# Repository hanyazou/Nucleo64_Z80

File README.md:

# Nucleo64 Z80

Nucleo64 Z80 is a Z80 expansion board for the STM32 Nucleo 64 board.
It adds a Z80 CPU and SRAM to the Nucleo.
The Z80's I/O access is handled by the STM32 MCU on the Nucleo.

## Features

- Simple 2-chip configuration with Z80 and SRAM, no additional logic IC needed
- Board test firmware includes Microsoft BASIC
- Faster Z80 CPU execution (clock up to 20MHz)
- I2C and SPI devices can be used with the Z80 (custom firmware required)

The Nucleo64 Z80 is derived from satoshiokue's MEZ80RAM and SuperMEZ80-CPM.

## Appearance

The white boards in the following pictures are the Nucleo64 Z80.

## Block Diagram

## Required Components

### ICs

- U3 Z80 (DIP 40 pin) *1
- U2 AS6C4008-55 SRAM 4Mbit (DIP 32 pin) *2

### Through-hole Components

- U3 IC socket (DIP 40 pin)
- U2 IC socket (DIP 32 pin)
- C1, C2 Capacitors 0.1uF
- R1 Resistor 200 ohms
- J4, J5 Pin headers (0.1" pitch 19x2 pin)
- D3, D4, D5 LEDs
- R6, R7, R8 Resistors 100 ohms 1/4W (resistor value may vary depending on the LED)

### Optional Components

- J3 SH 1.0 JST 4 pin connector *3
- J4, J5 Pin sockets (0.1" pitch 6x1 pin) *4

*1) Z80C0004 (4MHz) or higher recommended  
*2) 512Kbit (64KB) might be sufficient  
*3) For I2C Qwiic devices  
*4) For the micro SD card slot, use the one for ARM Arduino as shown on the following page:  
https://www.amazon.com/dp/B0B7WZQVHS

## Build Instructions

With fewer components, assembly is straightforward.
Solder all components except the 19x2 pin headers first, then solder the pin headers last.

## Board Test Firmware

The `FW/board_test` folder contains a test firmware project for STM32 CubeIDE.
The current target is STM32 Nucleo-64 STM32L476RG.

This firmware includes Microsoft BASIC.
When the Z80 runs at 20 MHz, executing ASCIIARTM.BAS takes 61 seconds.

The Z80 clock is generated by TIM5 in the STM32 L476RG.
The prescaler of TIM5 is set to 10 - 1, so the Z80 runs at 4 MHz, which is 1/20 of the system clock (80 MHz).
If you change the prescaler to 1, the clock will be 20 MHz.

## References

### SuperMEZ80-CPM

https://github.com/hanyazou/SuperMEZ80-CPM

### EMUZ80

https://vintagechips.wordpress.com/2022/03/05/emuz80_reference/

### MEZ80RAM

https://github.com/satoshiokue/MEZ80RAM

### NUCLEO-L476RG

https://www.st.com/en/evaluation-tools/nucleo-l476rg.html

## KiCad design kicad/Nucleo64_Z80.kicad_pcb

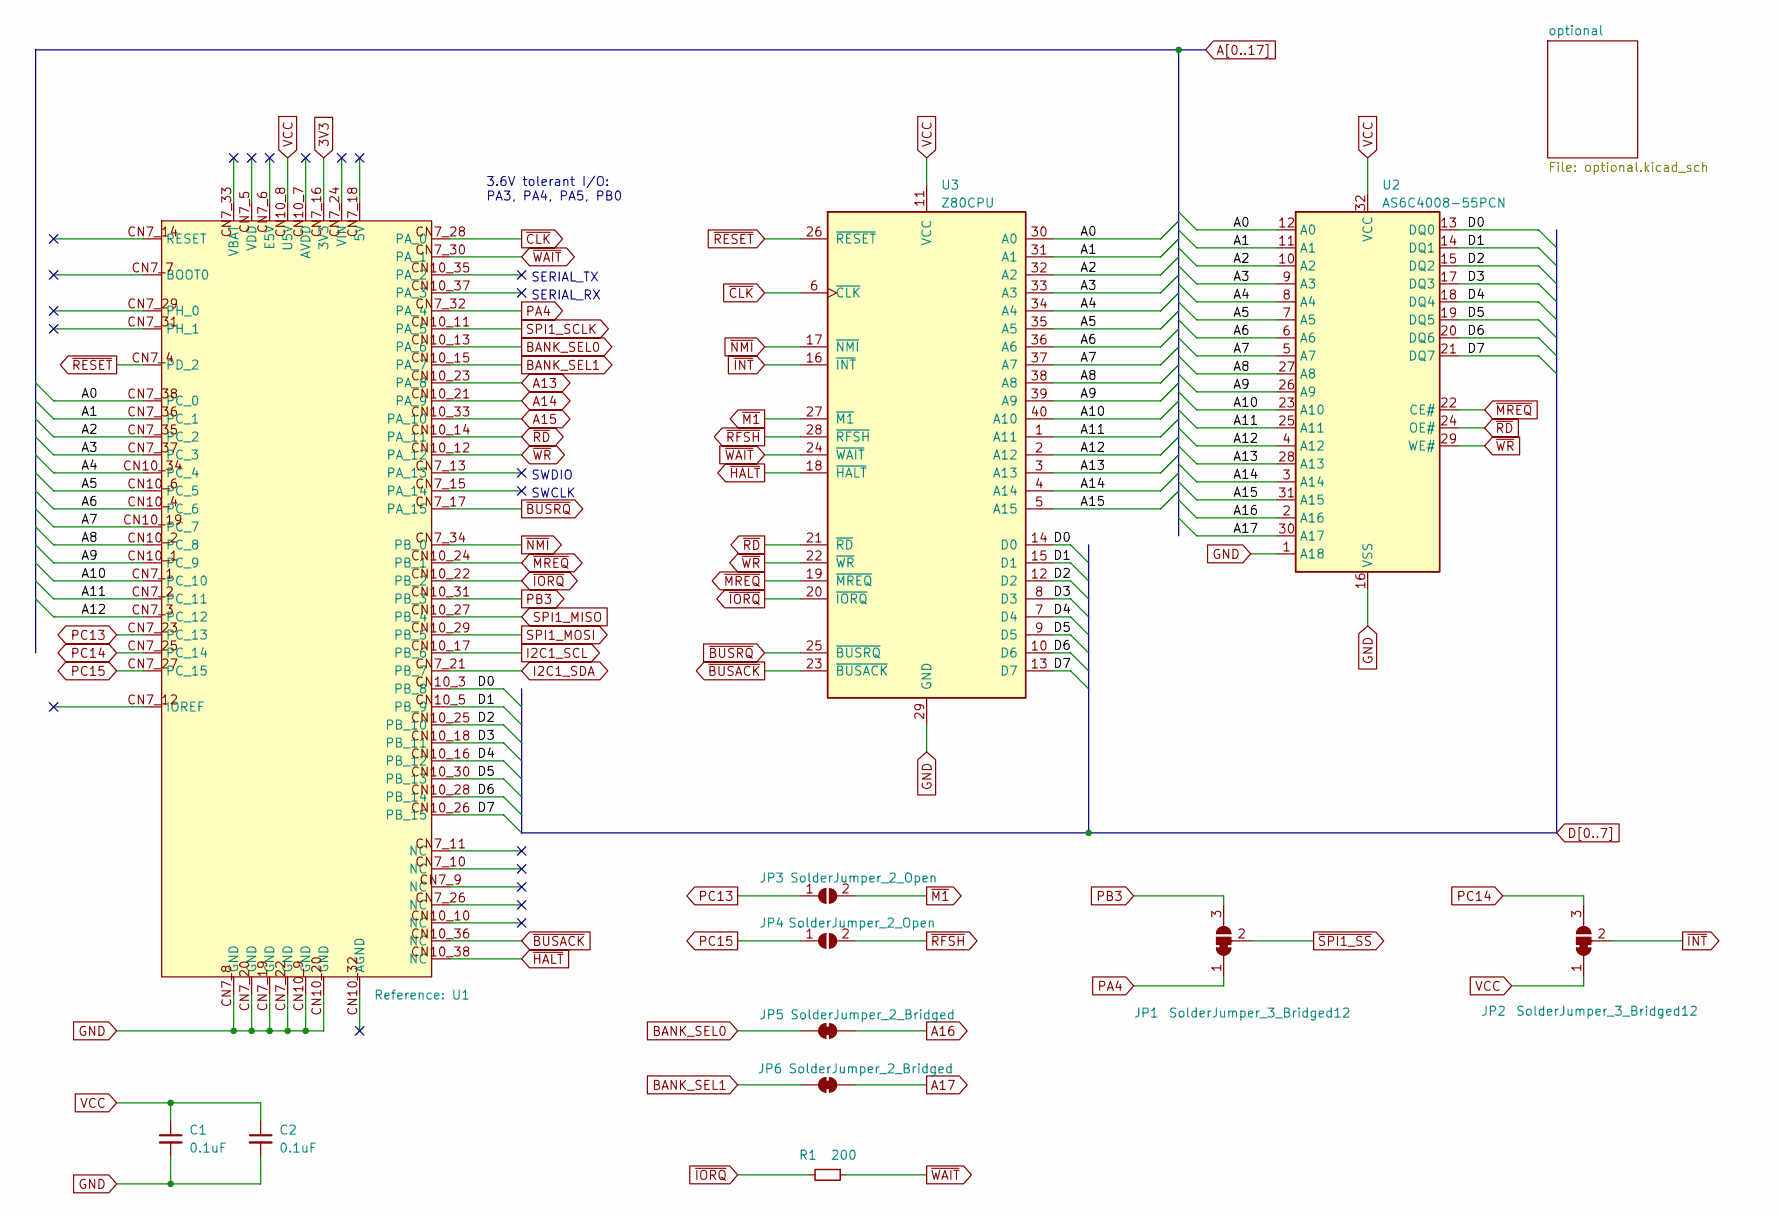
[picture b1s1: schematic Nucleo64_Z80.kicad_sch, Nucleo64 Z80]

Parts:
C1, C2: 0.1uF; C_Disc_D3.8mm_W2.6mm_P2.50mm
JP1, JP2: SolderJumper_3_Bridged12; SolderJumper-3_P1.3mm_Bridged12_RoundedPad1.0x1.5mm_NumberL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
JP3, JP4: SolderJumper_2_Open; SolderJumper-2_P1.3mm_Open_RoundedPad1.0x1.5mm
JP5, JP6: SolderJumper_2_Bridged; SolderJumper-2_P1.3mm_Bridged_RoundedPad1.0x1.5mm
R1: 200; R_Axial_DIN0204_L3.6mm_D1.6mm_P7.62mm_Horizontal
U1: NUCLEO64_morpho
U2: AS6C4008-55PCN; DIP-32_W15.24mm
U3: Z80CPU; DIP-40_W15.24mm

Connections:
3V3: U1.CN7_16 (3V3); also elsewhere on the board
A0: U1.CN7_38 (PC_0), U2.12 (A0), U3.30 (A0); also elsewhere on the board
A1: U1.CN7_36 (PC_1), U2.11 (A1), U3.31 (A1); also elsewhere on the board
A2: U1.CN7_35 (PC_2), U2.10 (A2), U3.32 (A2); also elsewhere on the board
A3: U1.CN7_37 (PC_3), U2.9 (A3), U3.33 (A3); also elsewhere on the board
A4: U1.CN10_34 (PC_4), U2.8 (A4), U3.34 (A4); also elsewhere on the board
A5: U1.CN10_6 (PC_5), U2.7 (A5), U3.35 (A5); also elsewhere on the board
A6: U1.CN10_4 (PC_6), U2.6 (A6), U3.36 (A6); also elsewhere on the board
A7: U1.CN10_19 (PC_7), U2.5 (A7), U3.37 (A7); also elsewhere on the board
A8: U1.CN10_2 (PC_8), U2.27 (A8), U3.38 (A8); also elsewhere on the board
A9: U1.CN10_1 (PC_9), U2.26 (A9), U3.39 (A9); also elsewhere on the board
A10: U1.CN7_1 (PC_10), U2.23 (A10), U3.40 (A10); also elsewhere on the board
A11: U1.CN7_2 (PC_11), U2.25 (A11), U3.1 (A11); also elsewhere on the board
A12: U1.CN7_3 (PC_12), U2.4 (A12), U3.2 (A12); also elsewhere on the board
A13: U1.CN10_23 (PA_8), U2.28 (A13), U3.3 (A13); also elsewhere on the board
A14: U1.CN10_21 (PA_9), U2.3 (A14), U3.4 (A14); also elsewhere on the board
A15: U1.CN10_33 (PA_10), U2.31 (A15), U3.5 (A15); also elsewhere on the board
A16: JP5.2 (B), U2.2 (A16); also elsewhere on the board
A17: JP6.2 (B), U2.30 (A17); also elsewhere on the board
BANK_SEL0: JP5.1 (A), U1.CN10_13 (PA_6); also elsewhere on the board
BANK_SEL1: JP6.1 (A), U1.CN10_15 (PA_7); also elsewhere on the board
D0: U1.CN10_3 (PB_8), U2.13 (DQ0), U3.14 (D0); also elsewhere on the board
D1: U1.CN10_5 (PB_9), U2.14 (DQ1), U3.15 (D1); also elsewhere on the board
D2: U1.CN10_25 (PB_10), U2.15 (DQ2), U3.12 (D2); also elsewhere on the board
D3: U1.CN10_18 (PB_11), U2.17 (DQ3), U3.8 (D3); also elsewhere on the board
D4: U1.CN10_16 (PB_12), U2.18 (DQ4), U3.7 (D4); also elsewhere on the board
D5: U1.CN10_30 (PB_13), U2.19 (DQ5), U3.9 (D5); also elsewhere on the board
D6: U1.CN10_28 (PB_14), U2.20 (DQ6), U3.10 (D6); also elsewhere on the board
D7: U1.CN10_26 (PB_15), U2.21 (DQ7), U3.13 (D7); also elsewhere on the board
GND: C1.2, C2.2, U1.CN7_8 (GND), U1.CN7_19 (GND), U1.CN7_20 (GND), U1.CN7_22 (GND), U1.CN10_9 (GND), U1.CN10_20 (GND), U2.1 (A18), U2.16 (VSS), U3.29 (GND); also elsewhere on the board
I2C1_SCL: U1.CN10_17 (PB_6); also elsewhere on the board
I2C1_SDA: U1.CN7_21 (PB_7); also elsewhere on the board
PA4: JP1.1 (A), U1.CN7_32 (PA_4)
PB3: JP1.3 (B), U1.CN10_31 (PB_3)
PC13: JP3.1 (A), U1.CN7_23 (PC_13)
PC14: JP2.3 (B), U1.CN7_25 (PC_14)
PC15: JP4.1 (A), U1.CN7_27 (PC_15)
SPI1_MISO: U1.CN10_27 (PB_4); also elsewhere on the board
SPI1_MOSI: U1.CN10_29 (PB_5); also elsewhere on the board
SPI1_SCLK: U1.CN10_11 (PA_5); also elsewhere on the board
VCC: C1.1, C2.1, JP2.1 (A), U1.CN10_8 (U5V), U2.32 (VCC), U3.11 (VCC); also elsewhere on the board
~BUSACK: U1.CN10_36 (NC), U3.23 (~BUSACK); also elsewhere on the board
~BUSRQ: U1.CN7_17 (PA_15), U3.25 (~BUSRQ); also elsewhere on the board
~CLK: U1.CN7_28 (PA_0), U3.6 (~CLK); also elsewhere on the board
~HALT: U1.CN10_38 (NC), U3.18 (~HALT); also elsewhere on the board
~INT: JP2.2 (C), U3.16 (~INT); also elsewhere on the board
~IORQ: R1.2, U1.CN10_22 (PB_2), U3.20 (~IORQ); also elsewhere on the board
~M1: JP3.2 (B), U3.27 (~M1); also elsewhere on the board
~MREQ: U1.CN10_24 (PB_1), U2.22 (CE#), U3.19 (~MREQ); also elsewhere on the board
~NMI: U1.CN7_34 (PB_0), U3.17 (~NMI); also elsewhere on the board
~RD: U1.CN10_14 (PA_11), U2.24 (OE#), U3.21 (~RD); also elsewhere on the board
~RESET: U1.CN7_4 (PD_2), U3.26 (~RESET); also elsewhere on the board
~RFSH: JP4.2 (B), U3.28 (~RFSH); also elsewhere on the board
~SPI1_SS: JP1.2 (C); also elsewhere on the board
~WAIT: R1.1, U1.CN7_30 (PA_1), U3.24 (~WAIT); also elsewhere on the board
~WR: U1.CN10_12 (PA_12), U2.29 (WE#), U3.22 (~WR); also elsewhere on the board

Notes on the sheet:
SWDIO
SERIAL_RX
SERIAL_TX
SWCLK
3.6V tolerant I/O: PA3, PA4, PA5, PB0

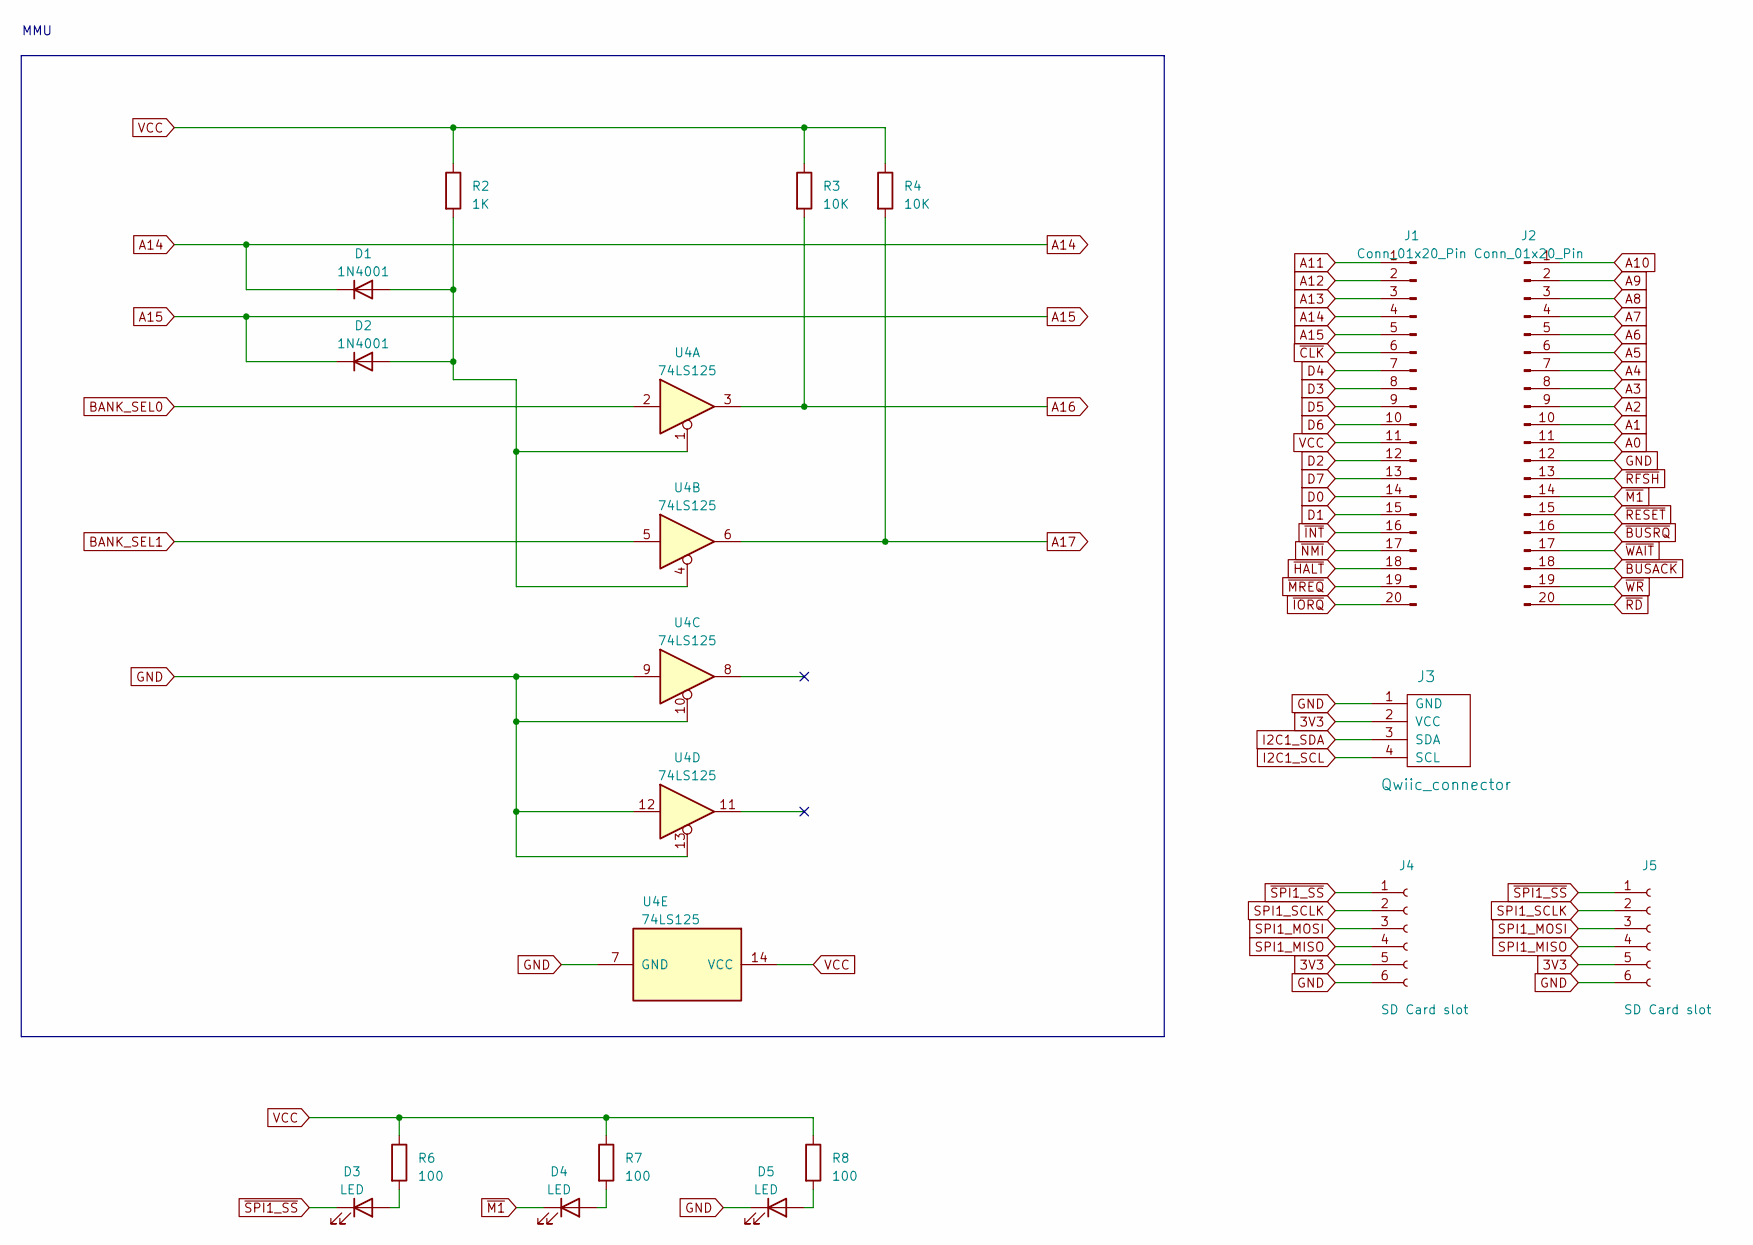
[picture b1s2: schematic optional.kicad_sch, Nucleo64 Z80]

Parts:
D1, D2: 1N4001; D_0805_2012Metric_Pad1.15x1.40mm_HandSolder
D3, D4, D5: LED; LED_D5.0mm
J1, J2: Conn_01x20_Pin; PinHeader_1x20_P2.54mm_Vertical
J3: Qwiic_connector; Qwiic_I2C_1.00mm_4pin
J4, J5: SD Card slot; PinHeader_1x06_P2.54mm_Vertical
R2: 1K; R_0805_2012Metric_Pad1.20x1.40mm_HandSolder
R3, R4: 10K; R_0805_2012Metric_Pad1.20x1.40mm_HandSolder
R6, R7, R8: 100; R_Axial_DIN0204_L3.6mm_D1.6mm_P7.62mm_Horizontal
U4: 74LS125; SSOP-14_5.3x6.2mm_P0.65mm

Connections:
3V3: J3.2 (VCC), J4.5, J5.5; also elsewhere on the board
A0: J2.11; also elsewhere on the board
A1: J2.10; also elsewhere on the board
A2: J2.9; also elsewhere on the board
A3: J2.8; also elsewhere on the board
A4: J2.7; also elsewhere on the board
A5: J2.6; also elsewhere on the board
A6: J2.5; also elsewhere on the board
A7: J2.4; also elsewhere on the board
A8: J2.3; also elsewhere on the board
A9: J2.2; also elsewhere on the board
A10: J2.1; also elsewhere on the board
A11: J1.1; also elsewhere on the board
A12: J1.2; also elsewhere on the board
A13: J1.3; also elsewhere on the board
A14: D1.1 (K), J1.4; also elsewhere on the board
A15: D2.1 (K), J1.5; also elsewhere on the board
A16: R3.2, U4.3; also elsewhere on the board
A17: R4.2, U4.6; also elsewhere on the board
BANK_SEL0: U4.2; also elsewhere on the board
BANK_SEL1: U4.5; also elsewhere on the board
D0: J1.14; also elsewhere on the board
D1: J1.15; also elsewhere on the board
D2: J1.12; also elsewhere on the board
D3: J1.8; also elsewhere on the board
D4: J1.7; also elsewhere on the board
D5: J1.9; also elsewhere on the board
D6: J1.10; also elsewhere on the board
D7: J1.13; also elsewhere on the board
GND: D5.1 (K), J2.12, J3.1 (GND), J4.6, J5.6, U4.7 (GND), U4.9, U4.10, U4.12, U4.13; also elsewhere on the board
I2C1_SCL: J3.4 (SCL); also elsewhere on the board
I2C1_SDA: J3.3 (SDA); also elsewhere on the board
unnamed: D1.2 (A), D2.2 (A), R2.2, U4.1, U4.4
unnamed: D3.2 (A), R6.2
unnamed: D4.2 (A), R7.2
unnamed: D5.2 (A), R8.2
SPI1_MISO: J4.4, J5.4; also elsewhere on the board
SPI1_MOSI: J4.3, J5.3; also elsewhere on the board
SPI1_SCLK: J4.2, J5.2; also elsewhere on the board
VCC: J1.11, R2.1, R3.1, R4.1, R6.1, R7.1, R8.1, U4.14 (VCC); also elsewhere on the board
~BUSACK: J2.18; also elsewhere on the board
~BUSRQ: J2.16; also elsewhere on the board
~CLK: J1.6; also elsewhere on the board
~HALT: J1.18; also elsewhere on the board
~INT: J1.16; also elsewhere on the board
~IORQ: J1.20; also elsewhere on the board
~M1: D4.1 (K), J2.14; also elsewhere on the board
~MREQ: J1.19; also elsewhere on the board
~NMI: J1.17; also elsewhere on the board
~RD: J2.20; also elsewhere on the board
~RESET: J2.15; also elsewhere on the board
~RFSH: J2.13; also elsewhere on the board
~SPI1_SS: D3.1 (K), J4.1, J5.1; also elsewhere on the board
~WAIT: J2.17; also elsewhere on the board
~WR: J2.19; also elsewhere on the board

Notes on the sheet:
MMU

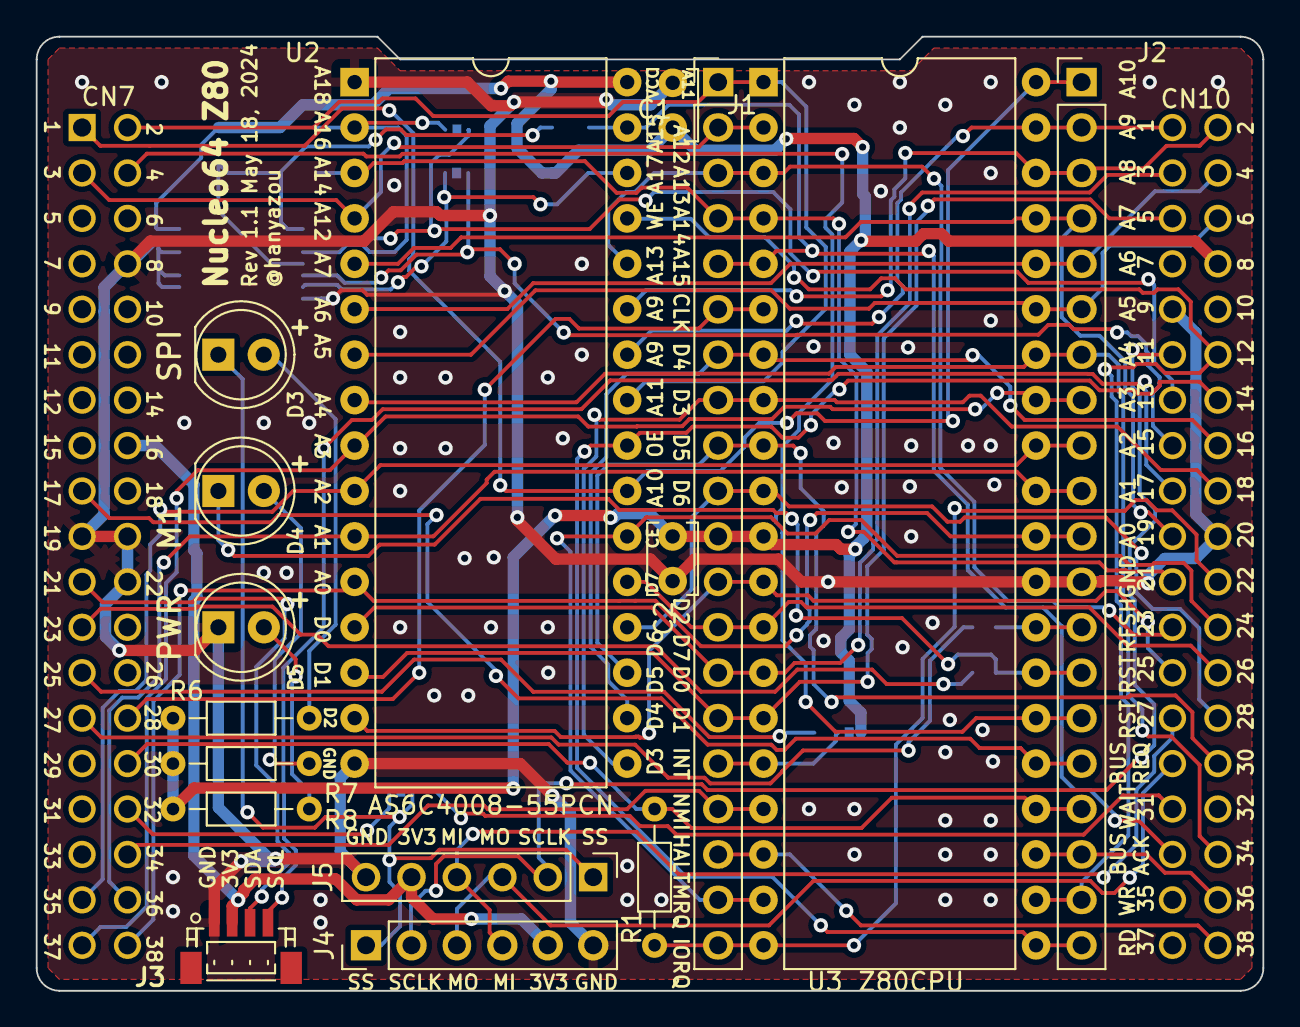
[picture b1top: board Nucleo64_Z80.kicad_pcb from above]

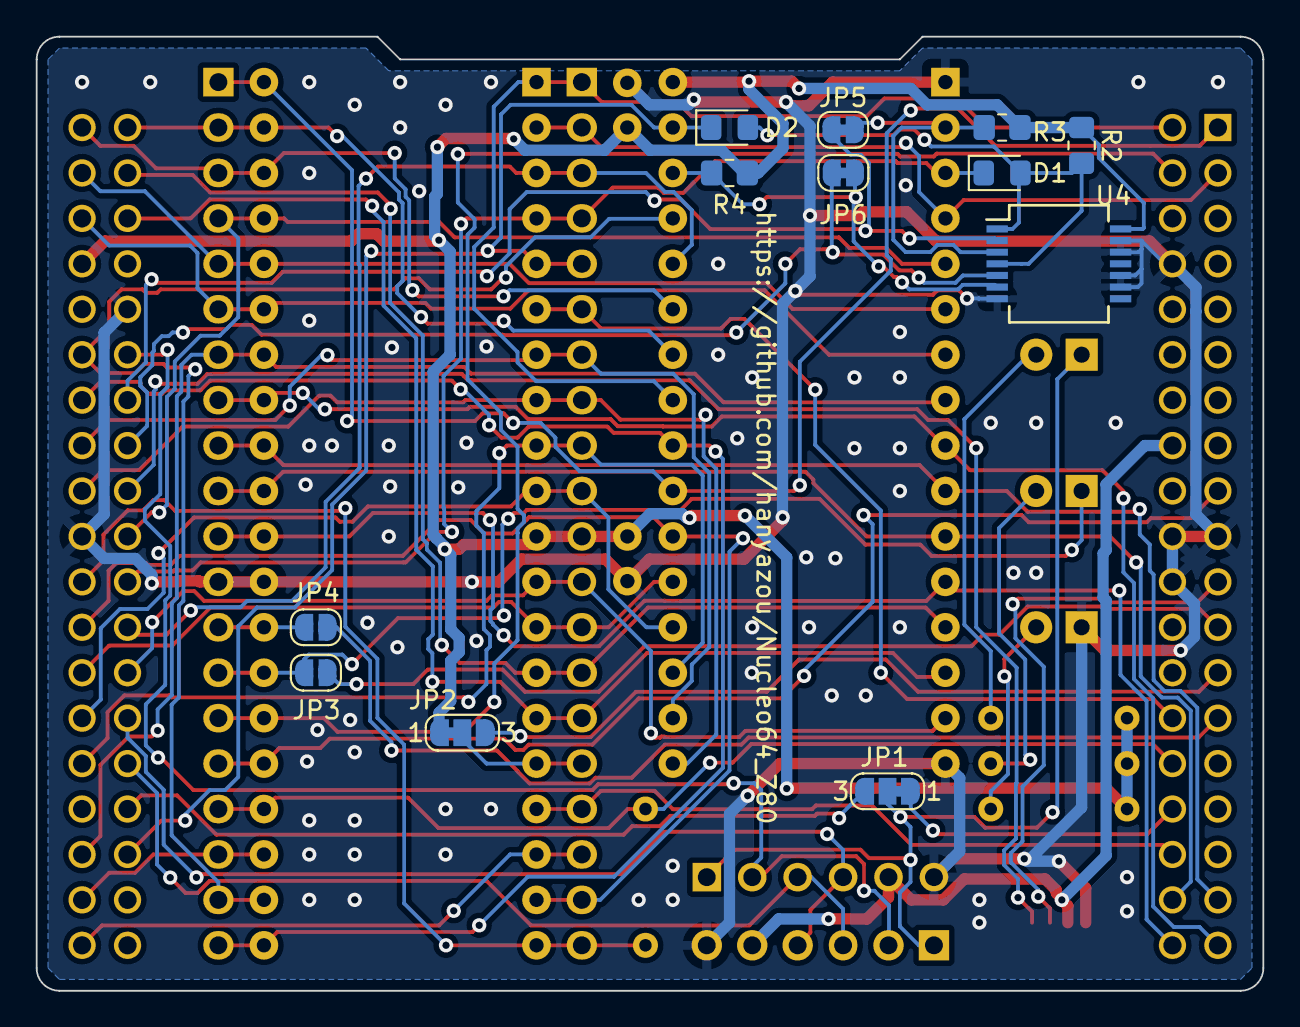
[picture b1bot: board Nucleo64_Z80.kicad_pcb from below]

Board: 2 copper layers, 68.6 x 53.3 mm, 29 parts (12 on the bottom side), 60 nets.

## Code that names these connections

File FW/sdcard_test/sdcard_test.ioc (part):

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Mcu.Name=STM32L476R(C-E-G)Tx
Mcu.Package=LQFP64
Mcu.UserName=STM32L476RGTx
PA0.Signal=S_TIM5_CH1
PA1.GPIOParameters=GPIO_PuPd,GPIO_Label
PA1.GPIO_Label=Z80_WAIT
PA1.GPIO_PuPd=GPIO_PULLUP
PA1.Signal=GPIO_Input
PA10.GPIOParameters=GPIO_PuPd,GPIO_Label
PA10.GPIO_Label=Z80_A15
PA10.GPIO_PuPd=GPIO_NOPULL
PA10.Signal=GPIO_Input
PA11.GPIOParameters=GPIO_PuPd,GPIO_Label
PA11.GPIO_Label=Z80_RD
PA11.GPIO_PuPd=GPIO_PULLUP
PA11.Signal=GPIO_Input
PA12.GPIOParameters=GPIO_PuPd,GPIO_Label
PA12.GPIO_Label=Z80_WR
PA12.GPIO_PuPd=GPIO_PULLUP
PA12.Signal=GPIO_Input
PA13\ (JTMS-SWDIO).GPIOParameters=GPIO_Label
PA13\ (JTMS-SWDIO).GPIO_Label=TMS
PA13\ (JTMS-SWDIO).Mode=Serial_Wire
PA13\ (JTMS-SWDIO).Signal=SYS_JTMS-SWDIO
PA14\ (JTCK-SWCLK).GPIOParameters=GPIO_Label
PA14\ (JTCK-SWCLK).GPIO_Label=TCK
PA14\ (JTCK-SWCLK).Mode=Serial_Wire
PA14\ (JTCK-SWCLK).Signal=SYS_JTCK-SWCLK
PA15\ (JTDI).GPIOParameters=GPIO_Label
PA15\ (JTDI).GPIO_Label=Z80_BUSRQ
PA15\ (JTDI).Signal=GPIO_Output
PA2.GPIOParameters=GPIO_Speed,GPIO_PuPd,GPIO_Label,GPIO_Mode
PA2.GPIO_Label=USART_TX
PA2.GPIO_Mode=GPIO_MODE_AF_PP
PA2.GPIO_PuPd=GPIO_NOPULL
PA2.GPIO_Speed=GPIO_SPEED_FREQ_VERY_HIGH
PA2.Mode=Asynchronous
PA2.Signal=USART2_TX
PA3.GPIOParameters=GPIO_Speed,GPIO_PuPd,GPIO_Label,GPIO_Mode
PA3.GPIO_Label=USART_RX
PA3.GPIO_Mode=GPIO_MODE_AF_PP
PA3.GPIO_PuPd=GPIO_NOPULL
PA3.GPIO_Speed=GPIO_SPEED_FREQ_VERY_HIGH
PA3.Mode=Asynchronous
PA3.Signal=USART2_RX
PA4.GPIOParameters=PinState,GPIO_Label
PA4.GPIO_Label=SPI1_SS
PA4.PinState=GPIO_PIN_SET
PA4.Signal=GPIO_Output
PA5.Mode=Full_Duplex_Master
PA5.Signal=SPI1_SCK
PA6.GPIOParameters=GPIO_Label
PA6.GPIO_Label=BANK_SEL0
PA6.Signal=GPIO_Output
PA7.GPIOParameters=GPIO_Label
PA7.GPIO_Label=BANK_SEL1
PA7.Signal=GPIO_Output
PA8.GPIOParameters=GPIO_Label
PA8.GPIO_Label=Z80_A13
PA8.Signal=GPIO_Input
PA9.GPIOParameters=GPIO_Label
PA9.GPIO_Label=Z80_A14
PA9.Signal=GPIO_Input
PB0.GPIOParameters=GPIO_Label
PB0.GPIO_Label=Z80_NMI
PB0.Signal=GPIO_Output
PB1.GPIOParameters=GPIO_PuPd,GPIO_Label
PB1.GPIO_Label=Z80_MEMRQ
PB1.GPIO_PuPd=GPIO_PULLUP
PB1.Signal=GPIO_Input
PB10.Signal=GPIO_Input
PB11.Signal=GPIO_Input
PB12.Signal=GPIO_Input
PB13.Signal=GPIO_Input
PB14.Signal=GPIO_Input
PB15.Signal=GPIO_Input
PB2.GPIOParameters=GPIO_PuPd,GPIO_Label
PB2.GPIO_Label=Z80_IOREQ
PB2.GPIO_PuPd=GPIO_PULLUP
PB2.Signal=GPIO_Input
PB4\ (NJTRST).Mode=Full_Duplex_Master
PB4\ (NJTRST).Signal=SPI1_MISO
PB5.Mode=Full_Duplex_Master
PB5.Signal=SPI1_MOSI
PB6.Mode=I2C
PB6.Signal=I2C1_SCL
PB7.Mode=I2C
PB7.Signal=I2C1_SDA
PB8.Signal=GPIO_Input
PB9.Signal=GPIO_Input
PC0.Signal=GPIO_Input
PC1.Signal=GPIO_Input
PC10.Signal=GPIO_Input
PC11.Signal=GPIO_Input
PC12.Signal=GPIO_Input
PC2.Signal=GPIO_Input
PC3.Signal=GPIO_Input
PC4.Signal=GPIO_Input
PC5.Signal=GPIO_Input
PC6.Signal=GPIO_Input
PC7.Signal=GPIO_Input
PC8.Signal=GPIO_Input
PC9.Signal=GPIO_Input
PD2.GPIOParameters=GPIO_Label
PD2.GPIO_Label=Z80_RESET
PD2.Signal=GPIO_Output
PH0-OSC_IN\ (PH0).Signal=RCC_OSC_IN
PH1-OSC_OUT\ (PH1).Signal=RCC_OSC_OUT
RCC.HSE_VALUE=8000000
RCC.SYSCLKFreq_VALUE=80000000
RCC.SYSCLKSource=RCC_SYSCLKSOURCE_PLLCLK
board=NUCLEO-L476RG
boardIOC=true

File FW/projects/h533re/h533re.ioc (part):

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Mcu.Name=STM32H533RETx
Mcu.Package=LQFP64
Mcu.UserName=STM32H533RETx
PA0.Signal=S_TIM2_CH1
PA1.GPIOParameters=GPIO_Label
PA1.GPIO_Label=Z80_IORQ
PA1.Signal=GPIO_Input
PA10.GPIOParameters=GPIO_Label
PA10.GPIO_Label=Z80_PWR_EN
PA10.Signal=GPIO_Output
PA11.Mode=Host
PA11.Signal=USB_DM
PA12.Mode=Host
PA12.Signal=USB_DP
PA15(JTDI).GPIOParameters=GPIO_Label
PA15(JTDI).GPIO_Label=Z80_NMI
PA15(JTDI).Signal=GPIO_Input
PA2.Mode=Asynchronous
PA2.Signal=USART2_TX
PA3.Mode=Asynchronous
PA3.Signal=USART2_RX
PA4.GPIOParameters=GPIO_Label
PA4.GPIO_Label=USB_FS_PWR_EN
PA4.Signal=GPIO_Output
PA5.GPIOParameters=GPIO_Label
PA5.GPIO_Label=BANK_SEL0
PA5.Signal=GPIO_Output
PA6.GPIOParameters=GPIO_Label
PA6.GPIO_Label=BANK_SEL1
PA6.Signal=GPIO_Output
PA7.GPIOParameters=GPIO_Label
PA7.GPIO_Label=Z80_INT
PA7.Signal=GPIO_Input
PA8.GPIOParameters=GPIO_Label
PA8.GPIO_Label=Z80_WAIT
PA8.Signal=GPIO_Input
PA9.GPIOParameters=GPIO_Label
PA9.GPIO_Label=SPI1_SS
PA9.Signal=GPIO_Output
PB0.GPIOParameters=GPIO_Label
PB0.GPIO_Label=Z80_D0
PB0.Signal=GPIO_Input
PB1.GPIOParameters=GPIO_Label
PB1.GPIO_Label=Z80_D1
PB1.Signal=GPIO_Input
PB10.Mode=I2C
PB10.Signal=I2C2_SCL
PB12.Mode=I2C
PB12.Signal=I2C2_SDA
PB13.GPIOParameters=GPIO_Label
PB13.GPIO_Label=Z80_A13
PB13.Signal=GPIO_Input
PB14.GPIOParameters=GPIO_Label
PB14.GPIO_Label=Z80_A14
PB14.Signal=GPIO_Input
PB15.GPIOParameters=GPIO_Label
PB15.GPIO_Label=Z80_A15
PB15.Signal=GPIO_Input
PB2.GPIOParameters=GPIO_Label
PB2.GPIO_Label=Z80_D2
PB2.Signal=GPIO_Input
PB3(JTDO/TRACESWO).GPIOParameters=GPIO_Label
PB3(JTDO/TRACESWO).GPIO_Label=Z80_D3
PB3(JTDO/TRACESWO).Signal=GPIO_Input
PB4(NJTRST).GPIOParameters=GPIO_Label
PB4(NJTRST).GPIO_Label=Z80_D4
PB4(NJTRST).Signal=GPIO_Input
PB5.GPIOParameters=GPIO_Label
PB5.GPIO_Label=Z80_D5
PB5.Signal=GPIO_Input
PB6.GPIOParameters=GPIO_Label
PB6.GPIO_Label=Z80_D6
PB6.Signal=GPIO_Input
PB7.GPIOParameters=GPIO_Label
PB7.GPIO_Label=Z80_D7
PB7.Signal=GPIO_Input
PB8.GPIOParameters=GPIO_Label
PB8.GPIO_Label=Z80_RD
PB8.Signal=GPIO_Input
PC0.GPIOParameters=GPIO_Label
PC0.GPIO_Label=Z80_A0
PC0.Signal=GPIO_Input
PC1.GPIOParameters=GPIO_Label
PC1.GPIO_Label=Z80_A1
PC1.Signal=GPIO_Input
PC10.GPIOParameters=GPIO_Label
PC10.GPIO_Label=Z80_A10
PC10.Signal=GPIO_Input
PC11.GPIOParameters=GPIO_Label
PC11.GPIO_Label=Z80_A11
PC11.Signal=GPIO_Input
PC12.GPIOParameters=GPIO_Label
PC12.GPIO_Label=Z80_A12
PC12.Signal=GPIO_Input
PC13.GPIOParameters=GPIO_Label
PC13.GPIO_Label=Z80_RESET
PC13.Signal=GPIO_Input
PC14-OSC32_IN(OSC32_IN).GPIOParameters=GPIO_Label
PC14-OSC32_IN(OSC32_IN).GPIO_Label=Z80_MREQ
PC14-OSC32_IN(OSC32_IN).Signal=GPIO_Input
PC15-OSC32_OUT(OSC32_OUT).GPIOParameters=GPIO_Label
PC15-OSC32_OUT(OSC32_OUT).GPIO_Label=Z80_WR
PC15-OSC32_OUT(OSC32_OUT).Signal=GPIO_Input
PC2.GPIOParameters=GPIO_Label
PC2.GPIO_Label=Z80_A2
PC2.Signal=GPIO_Input
PC3.GPIOParameters=GPIO_Label
PC3.GPIO_Label=Z80_A3
PC3.Signal=GPIO_Input
PC4.GPIOParameters=GPIO_Label
PC4.GPIO_Label=Z80_A4
PC4.Signal=GPIO_Input
PC5.GPIOParameters=GPIO_Label
PC5.GPIO_Label=Z80_A5
PC5.Signal=GPIO_Input
PC6.GPIOParameters=GPIO_Label
PC6.GPIO_Label=Z80_A6
PC6.Signal=GPIO_Input
PC7.GPIOParameters=GPIO_Label
PC7.GPIO_Label=Z80_A7
PC7.Signal=GPIO_Input
PC8.GPIOParameters=GPIO_Label
PC8.GPIO_Label=Z80_A8
PC8.Signal=GPIO_Input
PC9.GPIOParameters=GPIO_Label
PC9.GPIO_Label=Z80_A9
PC9.Signal=GPIO_Input
PD2.GPIOParameters=GPIO_Label
PD2.GPIO_Label=Z80_BUSRQ
PD2.Signal=GPIO_Input
RCC.HSE_VALUE=25000000
RCC.SYSCLKFreq_VALUE=248000000
RCC.SYSCLKSource=RCC_SYSCLKSOURCE_PLLCLK
board=custom

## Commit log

2024-03-24 Add Nucleo64_Z80 PCB revision 0.8
2024-03-25 Add .DS_Store to .gitignore
2024-03-25 Add FW/board_test
2024-03-25 fw: board_test: Flip SPI1_SS to blink DISK LED
2024-03-25 fw: board_test: Use printf() instead of HAL_UART_Transmit()
2024-03-25 fw: board_test: Add empty board_test()
2024-03-25 fw: board_test: Enable pull-pull of WAIT, IORQ, MREQ, RD and WR
2024-03-25 fw: board_test: Write tiny program to the SRAM and run it (WIP)
2024-03-30 fw: board_test: Enable PORTC in CubeMX
2024-03-30 fw: board_test: Write tiny program to the SRAM and run it (fixed)
2024-03-31 fw: board_test: Use TIM5 to generate Z80 clock
2024-03-31 fw: board_test: Fix UART I/O address
2024-04-28 fw: board_test: Fix WAIT pin settings
2024-04-28 fw: board_test: Add USART input
2024-04-28 tools: Add zasm module
2024-04-28 fw: roms: Add emubasic.asm
    repository: https://github.com/vintagechips/emuz80
    branch: https://github.com/vintagechips/emuz80/tree/main
    hash: 574ca1fee623a485bf5bc7ce2a298996df3a0c19
2024-04-28 fw: roms: emubasic: Add colons after labels
2024-04-28 fw: roms: emubasic: Use I/O instruction instread of memory mapped access
2024-04-28 fw: roms: emubasic: Add Makefile and emubasic.inc
2024-04-28 fw: board_test: Use emubasic.inc
2024-04-28 fw: board_test: Use TIM1 and delay_us()
2024-04-28 fw: board_test: Fix GPIO macro definitions
2024-05-11 Add Nucleo64_Z80 PCB revision 1.0
2024-05-11 fw: board_test: Fix pin assignment for PCB revision 1.0
2024-05-12 fw: Add .gitignore for STM32 IDE files
2024-05-12 fw: i2c_test: Add I2C scanner
2024-05-12 fw: i2c_test: Enable I2C1
2024-05-12 fw: Create new i2c_test from from board_test.ioc
2024-05-12 fw: i2c_test: Add DS1307 RTC test
2024-05-12 fw: i2c_test: Enable stdio and add delay_us()
2024-05-18 fw: sdcard_test: Copy main.c from i2c_test
2024-05-18 fw: Create new sdcard_test from i2c_test.ioc
2024-05-18 fw: sdcard_test: Enable SPI1
2024-05-18 fw: sdcard_test: Enable FATFS middleware
2024-05-18 fw: sdcard_test: Add user_diskio_spi.*
    repository: https://github.com/kiwih/cubeide-sd-card/tree/master/cubeide-sd-card/FATFS/Target
    files: cubeide-sd-card/FATFS/Target/user_diskio_spi.c, h
    branch: master
    commit: 521d07a40c
2024-05-18 fw: sdcard_test: Add FATFS sample code
    Tutorial: An SD card over SPI using STM32CubeIDE and FatFS
    https://01001000.xyz/2020-08-09-Tutorial-STM32CubeIDE-SD-card/
2024-05-18 fw: sdcard_test: Fix FATFS sample code
2024-05-18 Add Nucleo64_Z80 PCB revision 1.1
2024-05-18 fw: Ignore Debug and Release folders
2024-05-18 Add Nucleo64_Z80 PCB revision 1.2
2024-05-18 Add README
2025-12-28 fw: Create new project h503_usb_host_test
2025-12-29 fw: h503_usb_host_test: Enable USART3 as the debug serial
2025-12-29 fw: h503_usb_host_test: Add ThreadX and USBX
2025-12-29 fw: h503_usb_host_test: Display UX_MEMORY_INSUFFICIENT error
2025-12-29 fw: h503_usb_host_test: Add USB host and GPIO USB_FS_PWR_EN
2025-12-29 fw: h503_usb_host_test: Add USB Mass Storage Class
2025-12-29 fw: h503_usb_host_test: Call ux_host_stack_hcd_register() and HAL_HCD_Start()
2025-12-29 fw: h503_usb_host_test: Enable 1-way ICACHE
2025-12-29 fw: h503_usb_host_test: Fix USBX configuration parameters
2025-12-29 fw: h503_usb_host_test: Use TIM1 for the Timebase Source and use GPIO for Drive_VBUS_FS
2025-12-29 fw: h503_usb_host_test: Add FileX
2026-01-11 fw: h533_usb_host_test: Add FileX, ThreadX and USBX
2026-01-11 fw: h533_usb_host_test: Use TIM1 for the Timebase Source
2026-01-11 fw: h533_usb_host_test: Fix USBX configuration parameters
2026-01-11 fw: h533_usb_host_test: Call ux_host_stack_hcd_register() and HAL_HCD_Start()
2026-01-11 fw: h533_usb_host_test: Display USBX events adn errors
2026-01-11 fw: h533_usb_host_test: Call ux_host_stack_hcd_register() and HAL_HCD_Start() (fixed)
2026-01-11 fw: h533_usb_host_test: Fix USBX configuration parameters (fixed)
2026-01-17 fw: h533_usb_host_test: Add msc_test
2026-01-17 fw: h533_usb_host_test: Remove USBX Mass Storage Class support
2026-01-17 fw: h533_usb_host_test: msc_test.c (v2)
2026-01-17 fw: h533_usb_host_test: msc_test.c (v3)
2026-01-17 fw: h533_usb_host_test: msc_test.c (v4)
2026-01-17 fw: h533_usb_host_test: msc_test.c (v5)
2026-01-17 fw: h533_usb_host_test: msc_test.c (v6)
2026-01-17 fw: h533_usb_host_test: msc_test.c (v7)
2026-01-17 fw: h533_usb_host_test: msc_test.c (v8)
2026-01-18 fw: h533_usb_host_test: msc_test.c (v9)
2026-01-18 fw: h533_usb_host_test: msc_test.c (v10)
2026-01-18 fw: h533_usb_host_test: Read floppy disk sectors with READ(10)
2026-01-31 fw: Create new project h533re
2026-02-01 fw: h533re: Configure system clock and peripherals for board bring-up
    * USART2
    115200 8N1
    NVIC enable global interrupt
    GPIO PA2 USART2 TX
    GPIO PA3 USART2 RX
    * System Core
2026-02-01 fw: h533re: Regenerate code after updating CubeMX configuration
2026-02-01 fw: h533re: Enable printf() using USART2 debug serial
2026-02-01 fw: h533re: Add libraries imported by CubeMX
2026-02-01 fw: h533re: Fix USBX configuration parameters
2026-02-01 fw: h533re: Display USBX events and errors
2026-02-01 fw: h533re: Call ux_host_stack_hcd_register() and HAL_HCD_Start()
2026-02-01 WIP: fw: h533re: Add msc_test and read floppy disk sectors with READ(10)
2026-02-08 fw: nucleo64_z80: Add mem_init() to probe Z80 RAM and verify bank mapping
